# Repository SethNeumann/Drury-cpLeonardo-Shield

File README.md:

# REPO NAME: Drury-cpLeonardo-Shield

## License: Creative Commons Attribution-NonCommercial-ShareAlike

The original cpNode used a Leonardo-based protoyping board called a BB-Leo.  Chuck Catania like Leonardo because the
2nd serial port made for easier serial debugging as the cpNode needed D0/D1 (TX/RX) to implement the CMRINet.  In 2021
Modern Device discontinued the BB-Leo, so we moved the basic cpNode to the ProMini resulting in the cpNode-PM, we also made 
an adapter board with a Pro-Mini that fit into a standard cpNode, called a BB-ProMini.

Dennis Drury like the Leonardo and wanted to keep the code compatible, so he designed this shield form factor board that 
plugs onto a standard (Uno form factor) Leonardo.  It supports the I2C chain so you can use standard IOXs (or any other
shield you like if you want to write customer code).  

This is a great complement to cpNode, cpNode-PM, Andrew Deak's MegaNode and of course the classic JLC SMINI and SUSIC.

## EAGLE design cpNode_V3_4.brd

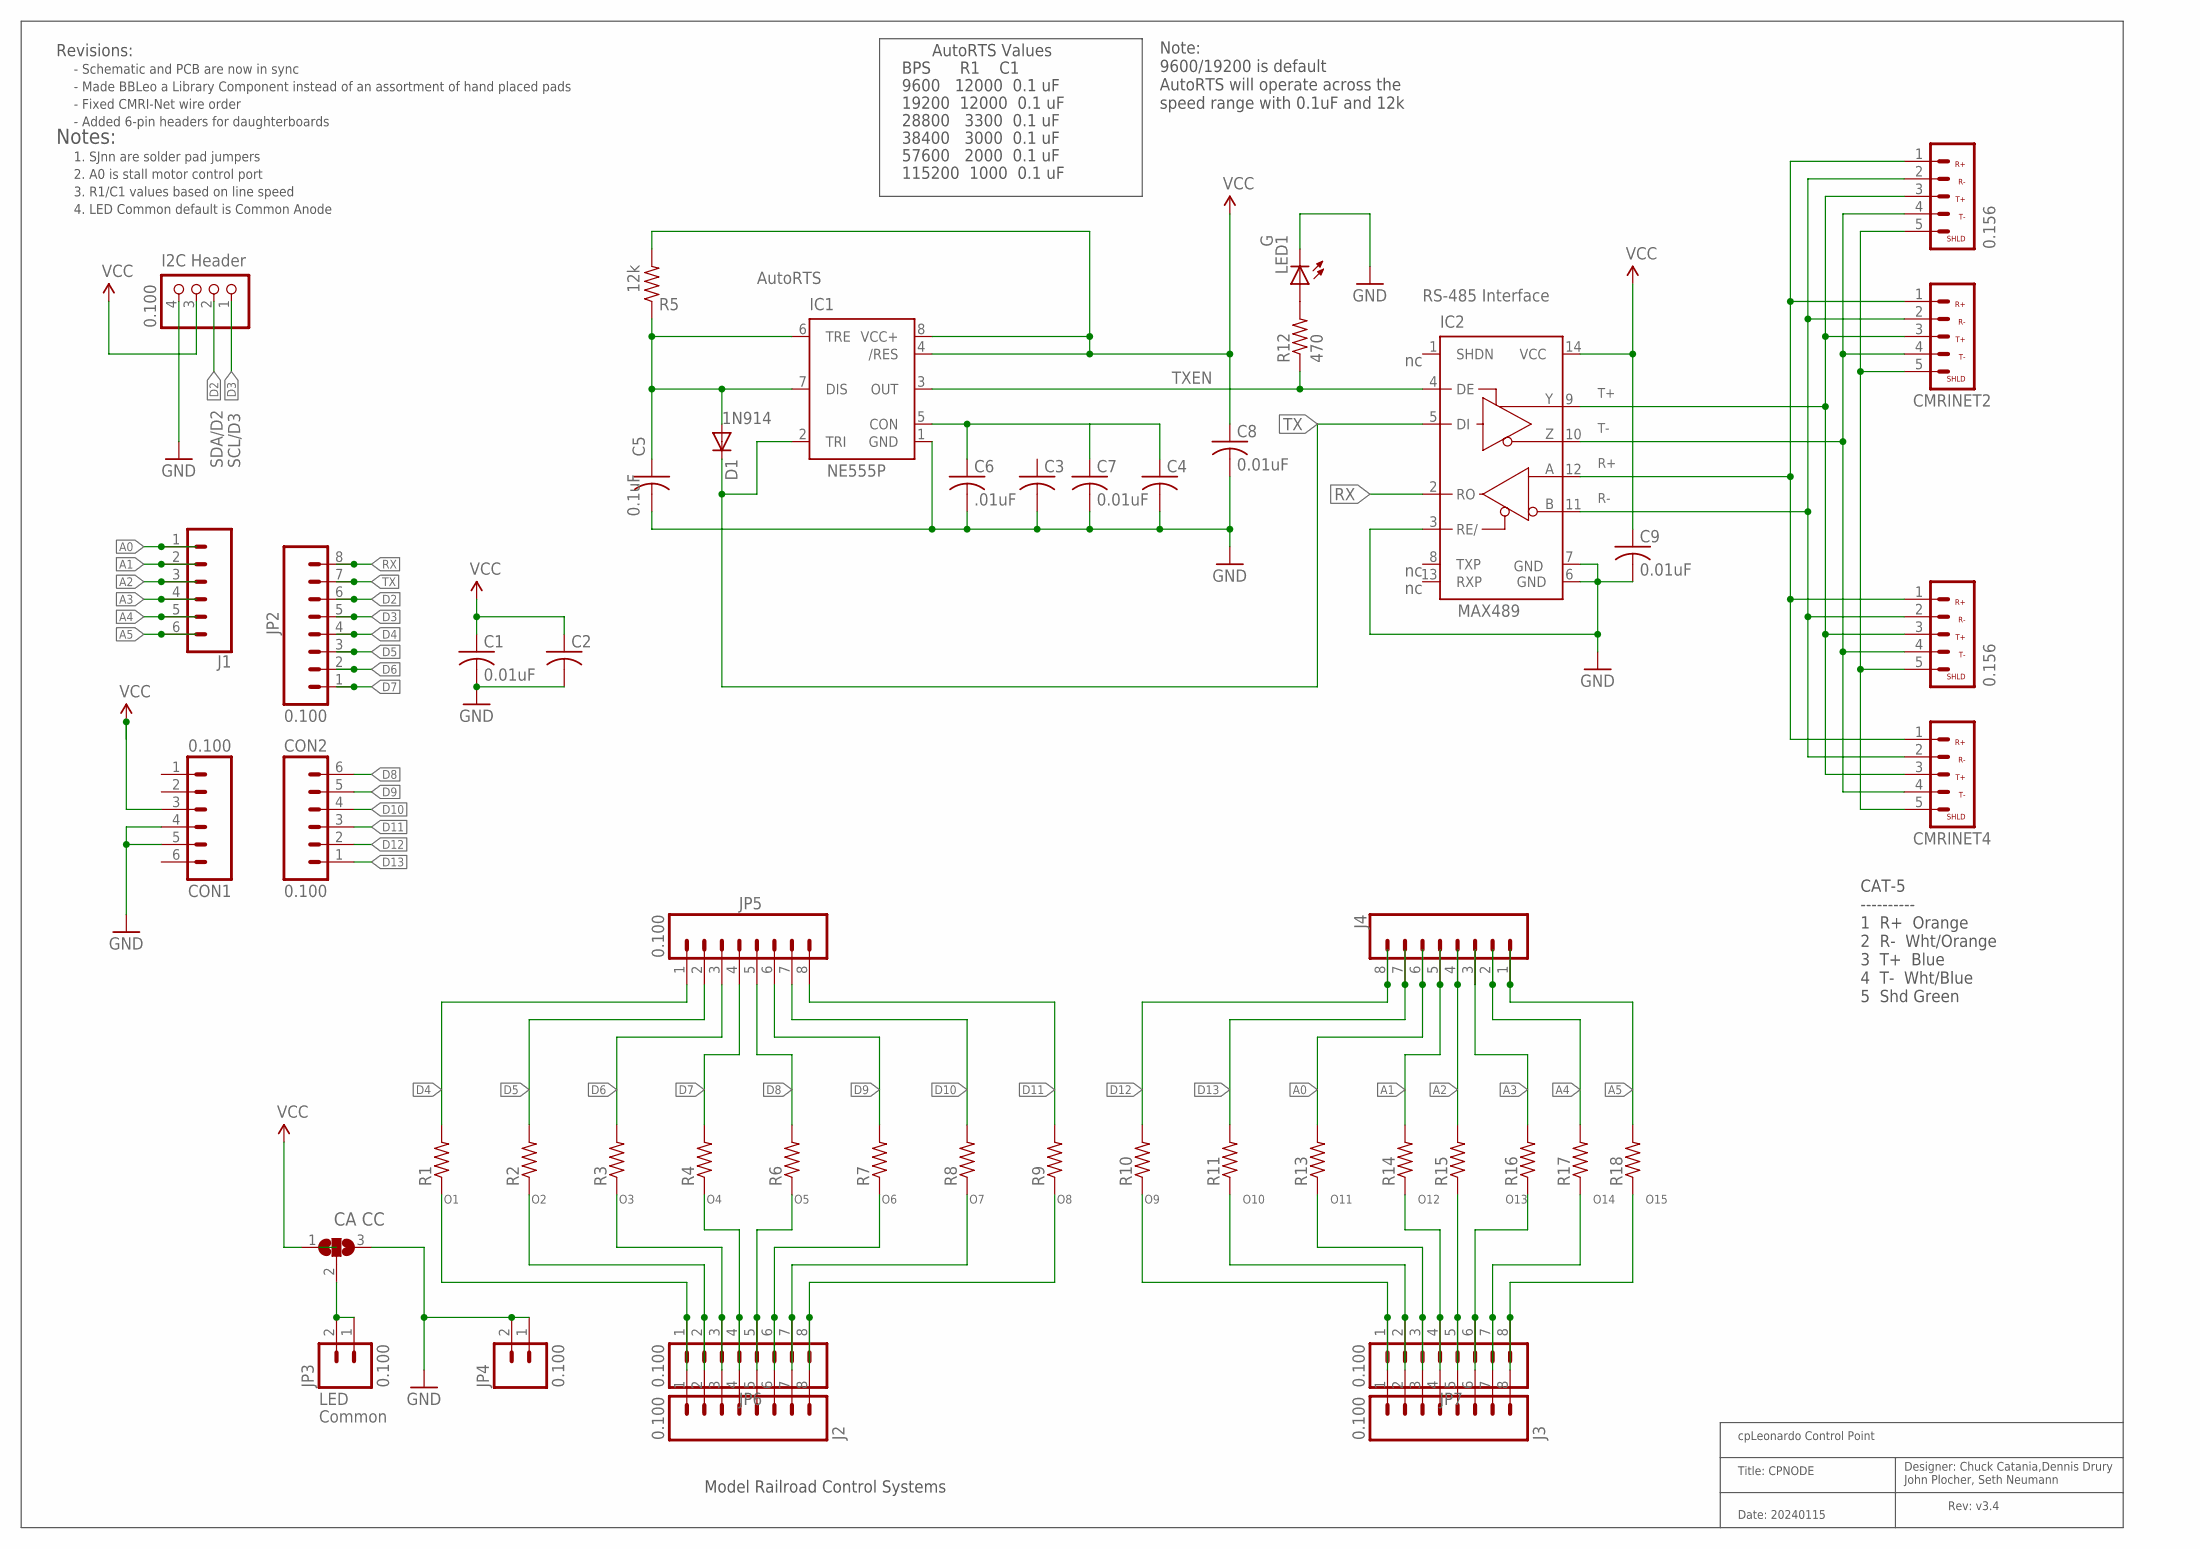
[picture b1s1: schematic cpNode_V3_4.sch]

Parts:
C1, C7, C8, C9: 0.01uF; C-PTH-0.100
C2, C3, C4: CAPPTH1; C050-024X044
C5: 0.1uF; C-PTH-0.100
C6: .01uF; C050-024X044
CMRINET1, CMRINET3: 0.156; KK-156-5
CMRINET2, CMRINET4: 3.5mm; CMRINET-3.5MM
CON1, CON2: 0.100; 1X06-SIP_LOCK
D1: 1N4148; DIODE-1N4148
IC1: NE555P; DIL-08
IC2: MAX3465CPD; DIL14
J1: CONN_06SILK_FEMALE_PTH; 1X06
J2, J3: 0.100; 1X08_LOCK_LONGPADS
J4: CONN_08"; 1X08
JP1: 0.100; 1X04/90
JP2, JP5, JP6, JP7: 0.100; 1X08
JP3, JP4: 0.100; MOLEX-1X2_LOCK
LED1: G; LED3MM
P1: CA CC; 3P-SMD-2X4.8
R1, R2, R3, R4, R6, R7, R8, R9, R10, R11, R13, R14, R15, R16, R17, R18: RPTH-R0; CUT-R
R5: 12k; AXIAL-0.4-RES
R12: 470; AXIAL-0.4-RES

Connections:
A0: J1.1, J4.6, R13.P1 (2)
A1: J1.2, J4.5, R14.P1 (2)
A2: J1.3, J4.4, R15.P1 (2)
A3: J1.4, J4.3, R16.P1 (2)
A4: J1.5, J4.2, R17.P1 (2)
A5: J1.6, J4.1, R18.P1 (2)
D2: JP1.2, JP2.6
D3: JP1.1, JP2.5
D4: JP2.4, JP5.1, R1.P1 (2)
D5: JP2.3, JP5.2, R2.P1 (2)
D6: JP2.2, JP5.3, R3.P1 (2)
D7: JP2.1, JP5.4, R4.P1 (2)
D8: CON2.6, JP5.5, R6.P1 (2)
D9: CON2.5, JP5.6, R7.P1 (2)
D10: CON2.4, JP5.7, R8.P1 (2)
D11: CON2.3, JP5.8, R9.P1 (2)
D12: CON2.2, J4.8, R10.P1 (2)
D13: CON2.1, J4.7, R11.P1 (2)
GND: C1.2, C2.2, C3.2, C4.2, C5.2, C6.2, C7.2, C8.2, C9.2, CON1.4, CON1.5, IC1.1 (GND), IC2.3 (RE/), IC2.6 (GND), IC2.7 (GND), JP1.4, JP4.1, JP4.2, LED1.K (C), P1.3
unnamed: LED1.A, R12.P$2 (2)
unnamed: C4.1, C6.1, C7.1, IC1.5 (CON)
unnamed: JP3.1, JP3.2, P1.2
unnamed: C5.1, D1.A, IC1.6 (TRE), IC1.7 (DIS), R5.P$1 (1)
unnamed: IC1.3 (OUT), IC2.4 (DE), R12.P$1 (1)
O1: J2.1, JP6.1, R1.P2 (1)
O2: J2.2, JP6.2, R2.P2 (1)
O3: J2.3, JP6.3, R3.P2 (1)
O4: J2.4, JP6.4, R4.P2 (1)
O5: J2.5, JP6.5, R6.P2 (1)
O6: J2.6, JP6.6, R7.P2 (1)
O7: J2.7, JP6.7, R8.P2 (1)
O8: J2.8, JP6.8, R9.P2 (1)
O9: J3.1, JP7.1, R10.P2 (1)
O10: J3.2, JP7.2, R11.P2 (1)
O11: J3.3, JP7.3, R13.P2 (1)
O12: J3.4, JP7.4, R14.P2 (1)
O13: J3.5, JP7.5, R15.P2 (1)
O14: J3.6, JP7.6, R16.P2 (1)
O15: J3.7, JP7.7, R17.P2 (1)
O16: J3.8, JP7.8, R18.P2 (1)
R+: CMRINET1.1, CMRINET2.1, CMRINET3.1, CMRINET4.1, IC2.12 (A)
R-: CMRINET1.2, CMRINET2.2, CMRINET3.2, CMRINET4.2, IC2.11 (B)
RX: IC2.2 (RO), JP2.8
SHIELD: CMRINET1.5, CMRINET2.5, CMRINET3.5, CMRINET4.5
T+: CMRINET1.3, CMRINET2.3, CMRINET3.3, CMRINET4.3, IC2.9 (Y)
T-: CMRINET1.4, CMRINET2.4, CMRINET3.4, CMRINET4.4, IC2.10 (Z)
TX: D1.C, IC1.2 (TRI), IC2.5 (DI), JP2.7
VCC: C1.1, C2.1, C8.1, C9.1, CON1.3, IC1.4 (/RES), IC1.8 (VCC+), IC2.14 (VCC), JP1.3, P1.1, R5.P$2 (2)

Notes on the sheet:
Rev: v3.4
Date: 20240115
Title: CPNODE
cpLeonardo Control Point
Designer: Chuck Catania,Dennis Drury John Plocher, Seth Neumann
SDA/D2
SCL/D3
TXEN
LED
1N914
MAX489
RS-485 Interface
Notes:
1. SJnn are solder pad jumpers
2. A0 is stall motor control port
I2C Header
3. R1/C1 values based on line speed
AutoRTS
AutoRTS Values
9600 12000 0.1 uF
19200 12000 0.1 uF
38400 3000 0.1 uF
57600 2000 0.1 uF
115200 1000 0.1 uF
BPS R1 C1
Common
4. LED Common default is Common Anode
Model Railroad Control Systems
Revisions:
CAT-5 ---------- 1 R+ Orange 2 R- Wht/Orange 3 T+ Blue 4 T- Wht/Blue 5 Shd Green
28800 3300 0.1 uF
Note: 9600/19200 is default AutoRTS will operate across the speed range with 0.1uF and 12k
- Fixed CMRI-Net wire order
- Schematic and PCB are now in sync
- Made BBLeo a Library Component instead of an assortment of hand placed pads
- Added 6-pin headers for daughterboards

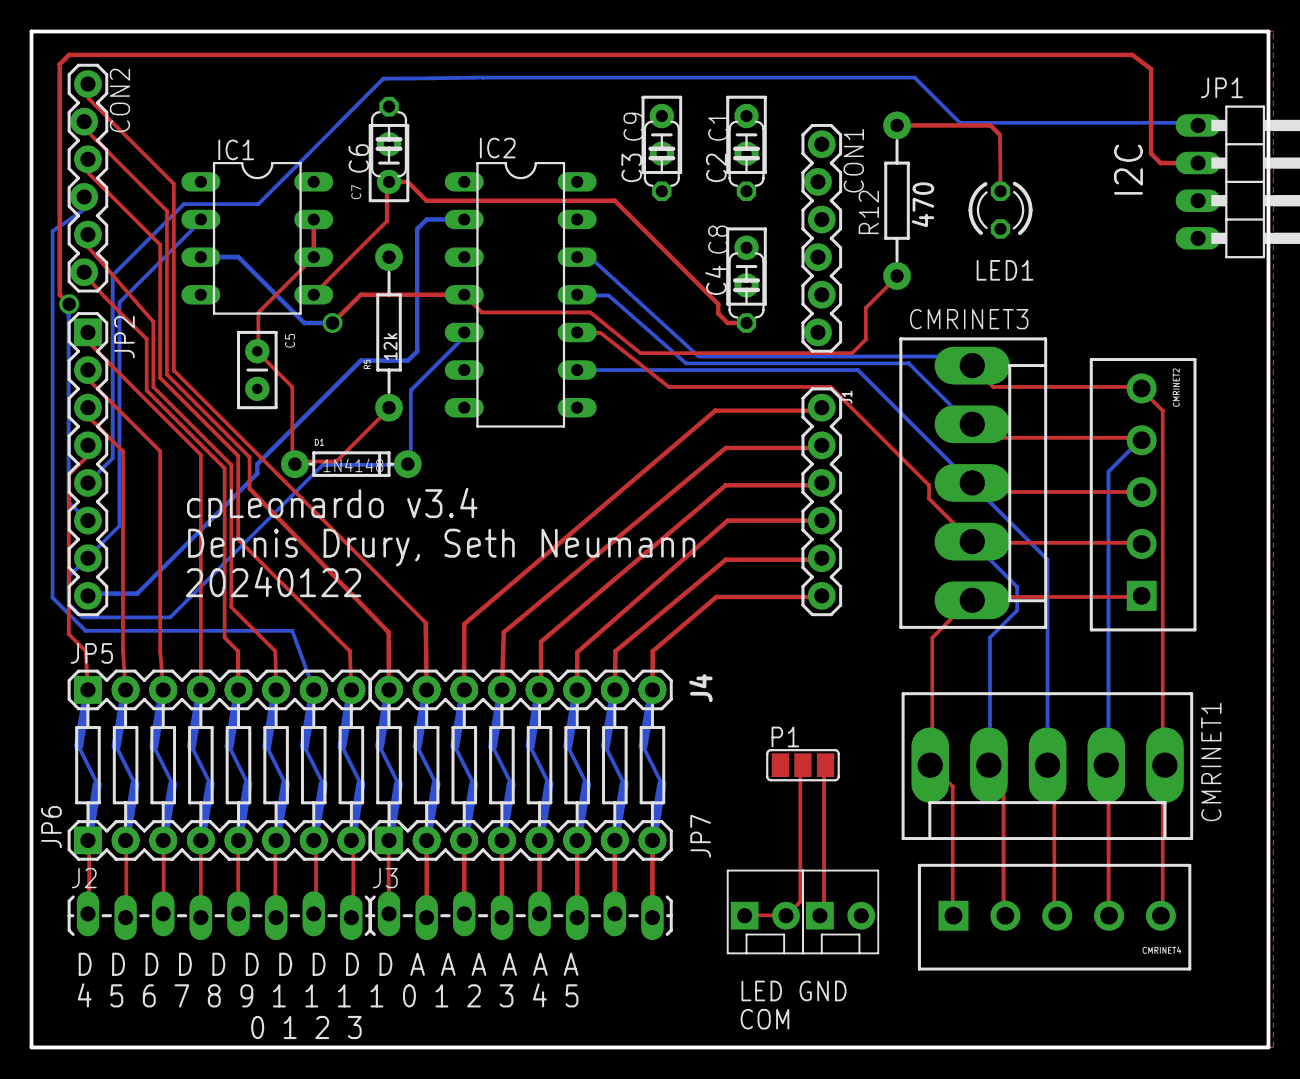
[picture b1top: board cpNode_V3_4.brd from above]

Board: 2 copper layers, 83.5 x 68.6 mm, 52 parts (1 on the bottom side), 48 nets.

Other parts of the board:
U$1: CA-PROP65WARNING
U$2: MRCSLOGOBTM
U$3: MRCSLOGOTOP

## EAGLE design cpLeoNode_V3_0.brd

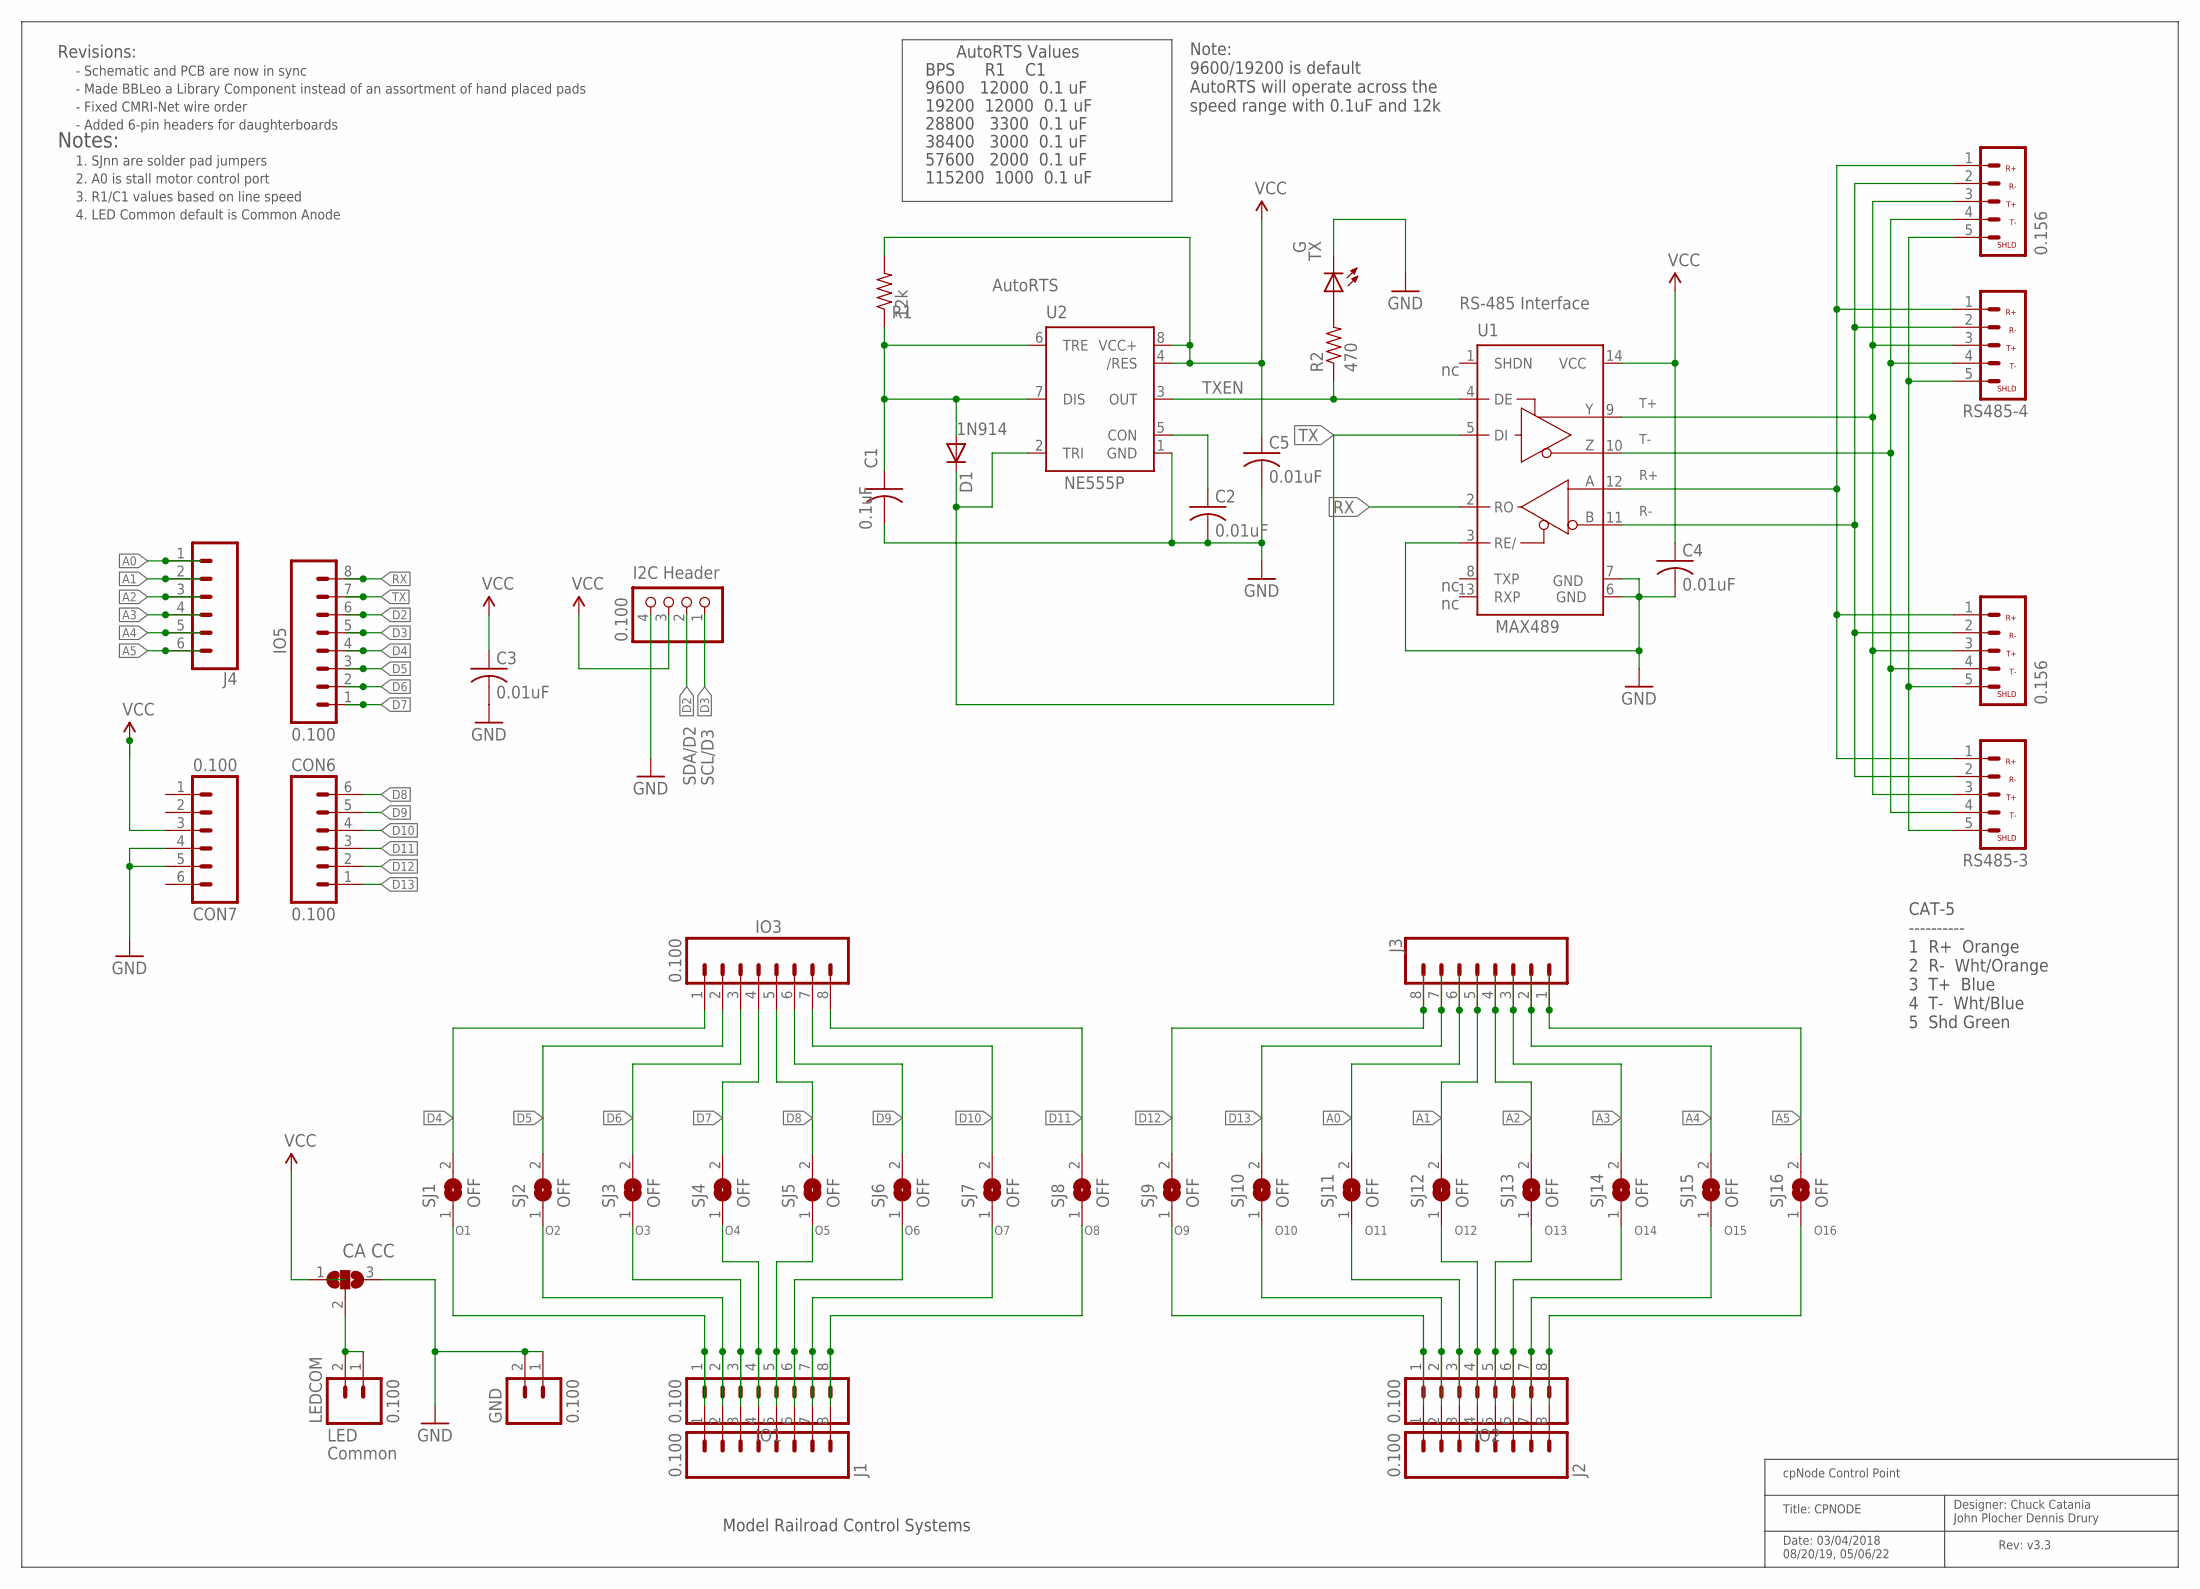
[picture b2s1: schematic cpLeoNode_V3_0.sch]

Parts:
C1: 0.1uF; C-PTH-0.100
C2, C3, C4, C5: 0.01uF; C-PTH-0.100
CON6, CON7: 0.100; 1X06-SIP_LOCK
D1: 1N4148; DIODE-1N4148
GND: 0.100; MOLEX-1X2_LOCK
I2CHDR: 0.100; 1X04/90
IO1, IO2, IO3, IO5: 0.100; 1X08
J1, J2: 0.100; 1X08_LOCK_LONGPADS
J3: CONN_08"; 1X08
J4: CONN_06SILK_FEMALE_PTH; 1X06
LEDCOM: 0.100; MOLEX-1X2_LOCK
P1: CA CC; 3P-SMD-2X4.8
R1: 12k; AXIAL-0.4-RES
R2: 470; AXIAL-0.4-RES
RS485-1, RS485-2: 0.156; KK-156-5
RS485-3, RS485-4: 3.5mm; CMRINET-3.5MM
SJ1, SJ2, SJ3, SJ4, SJ5, SJ6, SJ7, SJ8, SJ9, SJ10, SJ11, SJ12, SJ13, SJ14, SJ15, SJ16: OFF; SJ
TX: G; LED3MM
U1: MAX3465CPD; DIL14
U2: NE555P; DIL-08

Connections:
A0: J3.6, J4.1, SJ11.2
A1: J3.5, J4.2, SJ12.2
A2: J3.4, J4.3, SJ13.2
A3: J3.3, J4.4, SJ14.2
A4: J3.2, J4.5, SJ15.2
A5: J3.1, J4.6, SJ16.2
D2: I2CHDR.2, IO5.6
D3: I2CHDR.1, IO5.5
D4: IO3.1, IO5.4, SJ1.2
D5: IO3.2, IO5.3, SJ2.2
D6: IO3.3, IO5.2, SJ3.2
D7: IO3.4, IO5.1, SJ4.2
D8: CON6.6, IO3.5, SJ5.2
D9: CON6.5, IO3.6, SJ6.2
D10: CON6.4, IO3.7, SJ7.2
D11: CON6.3, IO3.8, SJ8.2
D12: CON6.2, J3.8, SJ9.2
D13: CON6.1, J3.7, SJ10.2
GND: C1.2, C2.2, C3.2, C4.2, C5.2, CON7.4, CON7.5, GND.1, GND.2, I2CHDR.4, P1.3, TX.K (C), U1.3 (RE/), U1.6 (GND), U1.7 (GND), U2.1 (GND)
unnamed: R2.P$2 (2), TX.A
unnamed: C2.1, U2.5 (CON)
unnamed: LEDCOM.1, LEDCOM.2, P1.2
unnamed: C1.1, D1.A, R1.P$1 (1), U2.6 (TRE), U2.7 (DIS)
unnamed: R2.P$1 (1), U1.4 (DE), U2.3 (OUT)
O1: IO1.1, J1.1, SJ1.1
O2: IO1.2, J1.2, SJ2.1
O3: IO1.3, J1.3, SJ3.1
O4: IO1.4, J1.4, SJ4.1
O5: IO1.5, J1.5, SJ5.1
O6: IO1.6, J1.6, SJ6.1
O7: IO1.7, J1.7, SJ7.1
O8: IO1.8, J1.8, SJ8.1
O9: IO2.1, J2.1, SJ9.1
O10: IO2.2, J2.2, SJ10.1
O11: IO2.3, J2.3, SJ11.1
O12: IO2.4, J2.4, SJ12.1
O13: IO2.5, J2.5, SJ13.1
O14: IO2.6, J2.6, SJ14.1
O15: IO2.7, J2.7, SJ15.1
O16: IO2.8, J2.8, SJ16.1
R+: RS485-1.1, RS485-2.1, RS485-3.1, RS485-4.1, U1.12 (A)
R-: RS485-1.2, RS485-2.2, RS485-3.2, RS485-4.2, U1.11 (B)
RX: IO5.8, U1.2 (RO)
SHIELD: RS485-1.5, RS485-2.5, RS485-3.5, RS485-4.5
T+: RS485-1.3, RS485-2.3, RS485-3.3, RS485-4.3, U1.9 (Y)
T-: RS485-1.4, RS485-2.4, RS485-3.4, RS485-4.4, U1.10 (Z)
TX: D1.C, IO5.7, U1.5 (DI), U2.2 (TRI)
VCC: C3.1, C4.1, C5.1, CON7.3, I2CHDR.3, P1.1, R1.P$2 (2), U1.14 (VCC), U2.4 (/RES), U2.8 (VCC+)

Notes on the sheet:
Rev: v3.3
Date: 03/04/2018 08/20/19, 05/06/22
Title: CPNODE
cpNode Control Point
Designer: Chuck Catania John Plocher Dennis Drury
SDA/D2
SCL/D3
TXEN
LED
1N914
MAX489
RS-485 Interface
Notes:
1. SJnn are solder pad jumpers
2. A0 is stall motor control port
I2C Header
3. R1/C1 values based on line speed
AutoRTS
AutoRTS Values
9600 12000 0.1 uF
19200 12000 0.1 uF
38400 3000 0.1 uF
57600 2000 0.1 uF
115200 1000 0.1 uF
BPS R1 C1
Common
4. LED Common default is Common Anode
Model Railroad Control Systems
Revisions:
CAT-5 ---------- 1 R+ Orange 2 R- Wht/Orange 3 T+ Blue 4 T- Wht/Blue 5 Shd Green
28800 3300 0.1 uF
Note: 9600/19200 is default AutoRTS will operate across the speed range with 0.1uF and 12k
- Fixed CMRI-Net wire order
- Schematic and PCB are now in sync
- Made BBLeo a Library Component instead of an assortment of hand placed pads
- Added 6-pin headers for daughterboards

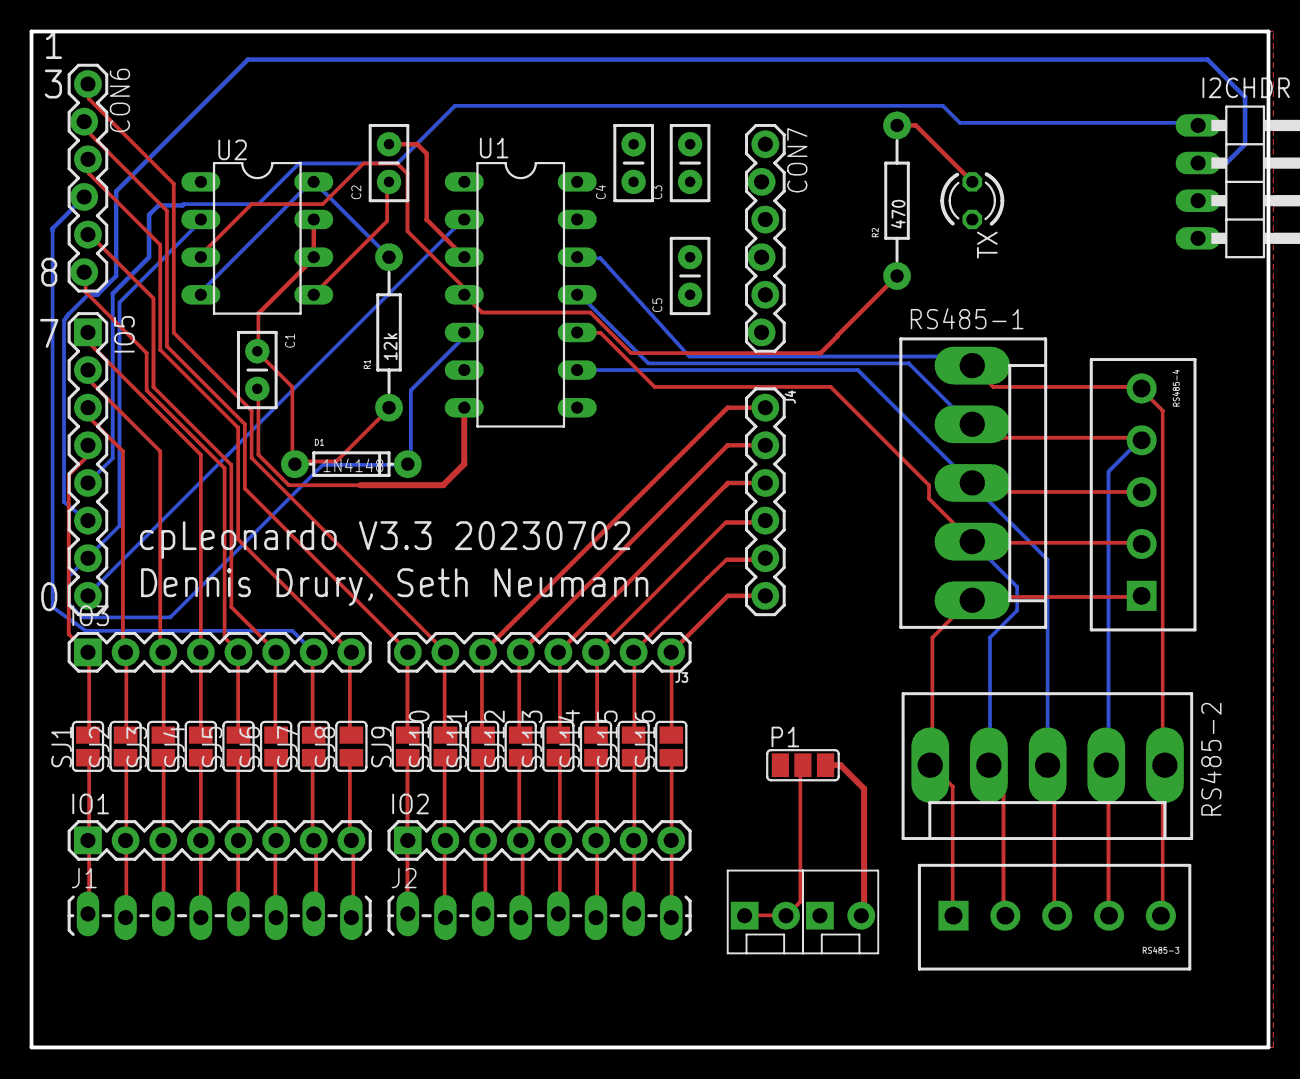
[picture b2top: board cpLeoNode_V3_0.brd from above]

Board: 2 copper layers, 83.5 x 68.6 mm, 47 parts (0 on the bottom side), 48 nets.

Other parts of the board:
U$1: CA-PROP65WARNING
U$2: MRCSLOGOBTM

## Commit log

2022-05-10 integrating files from Dennis
    This Dennis' original file with a ground plane added
2022-07-05 adjustments of Leonardo header to fit better
2022-07-05 removed random gerb files
2023-07-03 A bunch of cleanup after moving things around
    1 - move Arduino connectors closer together for better fit with the Leonardo
    2 - added VCC plane and removed a lot of old VCC and GND traces
    3- added labels on top to help orient Leonardo
    4 - mirrored bottom labels and moved to bplace for readability
2024-02-13 version 3.4
    moved to cuttable resistors

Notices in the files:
parts and their libraries:
SparkFun-Connectors: Licensing: Creative Commons ShareAlike 4.0 International - https://creativecommons.org/licenses/by-sa/4.0
